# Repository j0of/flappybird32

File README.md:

# Flappybird32
Mini flappybird console implemented using ESP32 and Arduino framework.

https://github.com/user-attachments/assets/f266951c-387f-4cfc-aca1-4248d2725a74

# Components
- ESP-WROOM32
- Dollatek 1.8' 128x160 RGB TFT_LCD (ST7735)
-  Push button
-  Slide switch
-  Passive Buzzer
-  10k ohm resistor

# Wiring
| ESP32 Pin | Component |
| --- | --- |
| D14 | TFT SCL |
| D27 | TFT SDA |
| D26 | TFT RES |
| D25 | TFT DC |
| D33 | TFT CS |
| D16 | Push button (A) |
| D19 | Slide switch (Middle) |

5V  ----- TFT VCC

GND ----- TFT GND

GND ----- 10k ohms ----- Button (B)

GND ----- (-) Passive buzzer (+) ----- Slide switch (B)

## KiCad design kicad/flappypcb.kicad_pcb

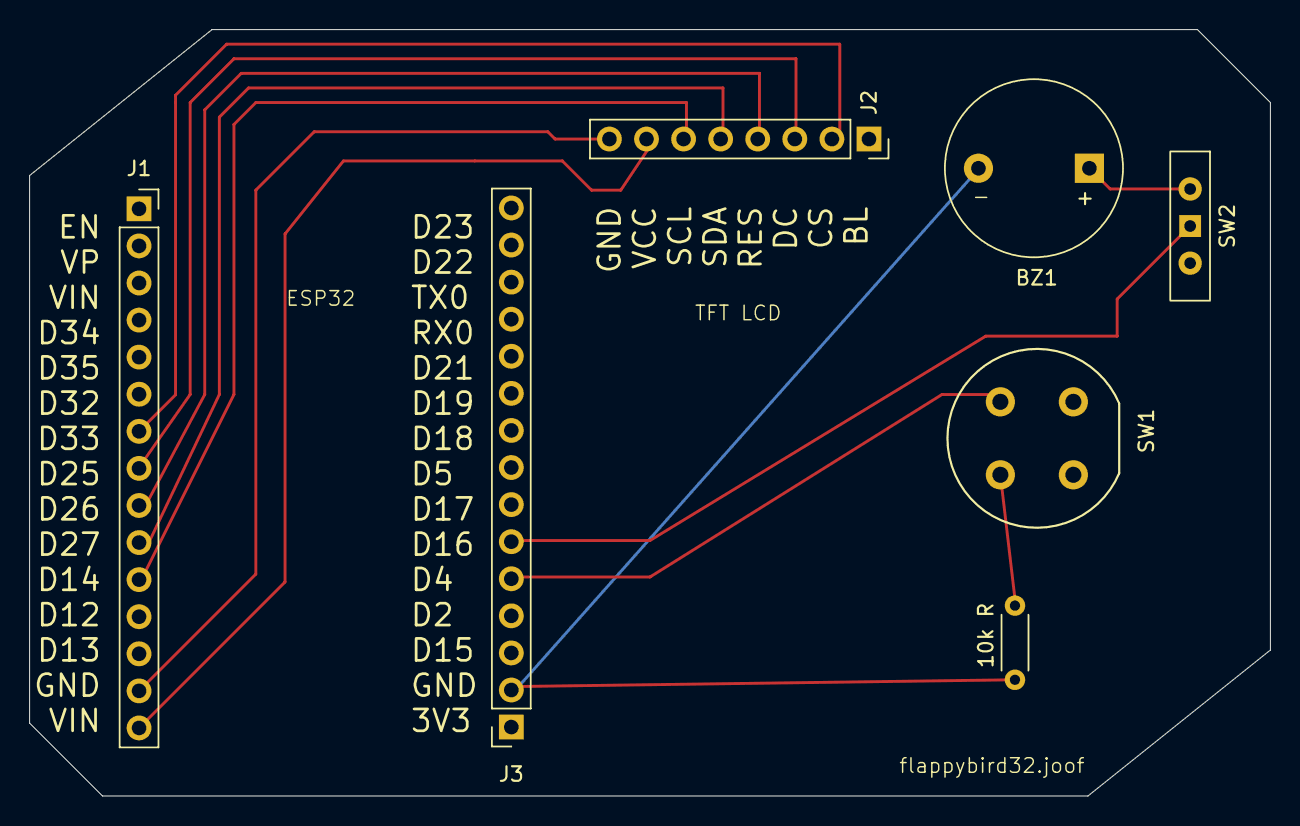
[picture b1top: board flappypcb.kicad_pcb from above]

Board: 2 copper layers, 85.0 x 52.5 mm, 7 parts (0 on the bottom side), 12 nets.

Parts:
10k R: 10k R; R_Axial_DIN0204_L3.6mm_D1.6mm_P5.08mm_Horizontal
BZ1: Buzzer; Buzzer_12x9.5RM7.6
J1, J3: Conn_01x15_Socket; PinSocket_1x15_P2.54mm_Vertical
J2: Conn_01x08_Socket; PinSocket_1x08_P2.54mm_Vertical
SW1: SW_Push_Dual; Push_E-Switch_KS01Q01
SW2: SW_Wuerth_450301014042; SW_Slide-03_Wuerth-WS-SLTV_10x2.5x6.4_P2.54mm

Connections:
unnamed: BZ1.1 (+), SW2.2 (C)
unnamed: 10k R.1, BZ1.2 (-), J3.2
unnamed: J1.7, J2.2
unnamed: J1.8, J2.3
unnamed: J1.9, J2.4
unnamed: J1.10, J2.5
unnamed: J1.11, J2.6
unnamed: J1.14, J2.8
unnamed: J1.15, J2.7
unnamed: J3.5, SW1.2
unnamed: J3.6, SW2.1 (B)
unnamed: 10k R.2, SW1.1

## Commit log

2025-10-12 minor change
2025-10-13 Added jump debounce + more minor changes
2025-10-13 Minor changes
2025-11-01 Pin changes
2025-11-02 Add KiCAD project files for PCB
2025-11-14 Edited pinout
2025-11-15 Major codebase refactoring; Added remote control via web server and websockets with WiFi access point
2025-11-15 Edited WebController
